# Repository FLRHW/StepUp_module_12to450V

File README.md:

<p align="center" width="100%">
  
</p>

***

<p align="center">
  
&nbsp; &nbsp; &nbsp; &nbsp;
  
</p>

***

# **StepUp_module_12to450V**
This repository contains a reverse‑engineered KiCad schematic and PCB layout from a commercial module originally purchased from AliExpress.

## Project overview
This project documents the electrical design and PCB layout of a third‑party module by recreating them from scratch in KiCad for learning, repair, and interoperability purposes. The repository does not include any original vendor design files, firmware, branding, or trademarks.

## Origin and scope
Original hardware: generic module purchased from AliExpress (exact vendor and listing may change over time, the following terms can help finding similar modules: "70W DC-DC 12V 24V To 200V-450V Voltage Adjustable Boost Power Converter Nixie Clock Tube Amplifier Capacitor Charging").  
Status: unofficial, reverse‑engineered reference design; not affiliated with, endorsed by, or supported by the original manufacturer or seller.  
Contents: KiCad schematic, PCB layout, netlists, and supporting documentation created from measurements and inspection of a physical unit.

## Intended use
This repository is intended for:
* Educational use and study of the circuit;
* Repair, modification, or replacement of compatible hardware;
* Integration into hobby or research projects, subject to any third‑party IP that may apply in your jurisdiction. Users are responsible for checking any patent, copyright, or regulatory constraints that may apply to their own use.

## License
The KiCad design files and documentation in this repository are released under the CERN Open Hardware Licence v2 – Permissive (CERN‑OHL‑P‑2.0). SPDX identifier: CERN-OHL-P-2.0 See the LICENSE file for the full legal text and conditions.  
In short and non‑legal terms, you are free to use, modify, manufacture, and distribute hardware based on these files, provided you respect attribution requirements and the terms in the license.

## Trademarks and third‑party rights
All product names, logos, and brands of the original module are the property of their respective owners and are not included or licensed here.  
Any reference to third‑party marks is purely descriptive and does not imply endorsement or affiliation.  
If you are the rights holder for the original hardware and have concerns about this documentation, please open an issue in the repository.

## Safety and disclaimer
* The design is provided as is, with no warranty of any kind;
* Use it at your own risk; always review the schematic, layout, and component ratings before using it;
* High voltage can cause injury, death, or damage to equipment; ensure appropriate protections and testing procedures.

## Contributing
Contributions are welcome. Please use pull requests and issues to propose changes or discuss potential improvements.

***

## DIRECTORY STRUCTURE
    │
    ├─ Computations       # Misc calculations
    ├─ HTML               # HTML files for generated webpage
    ├─ Images             # Pictures and renders
    │
    ├─ kibot_resources    # External resources for KiBot
    │  ├─ colors          # Color theme for KiCad
    │  ├─ fonts           # Fonts used in the project
    │  ├─ scripts         # External scripts used with KiBot
    │  └─ templates       # Templates for KiBot generated reports
    │
    ├─ kibot_yaml         # KiBot YAML config files
    ├─ KiRI               # KiRI (PCB diff viewer) files
    │
    ├─ lib                # KiCad footprint and symbol libraries
    │  ├─ 3d_models       # Component 3D models
    │  ├─ lib_fp          # Footprint libraries
    │  └─ lib_sym         # Symbol libraries
    │
    ├─ Logos              # Logos
    │
    ├─ Manufacturing      # Assembly and fabrication documents
    │  ├─ Assembly        # Assembly documents (BoM, pos, notes)
    │  │
    │  └─ Fabrication     # Fabrication documents (ZIP, notes)
    │     ├─ Drill Tables # CSV drill tables
    │     └─ Gerbers      # Gerbers
    │
    ├─ Report             # Reports for ERC/DRC
    ├─ Schematic          # PDF of schematic
    ├─ Supporting docs    # Measurement data
    │  ├─ 11.66 kOhm load # Scope captures
    │  └─ 870 Ohm load    # Scope captures
    │
	├─ Templates          # Title block templates
    ├─ Testing
    │  └─ Testpoints      # Testpoints tables      
    │
    └─ Variants           # Outputs for assembly variants

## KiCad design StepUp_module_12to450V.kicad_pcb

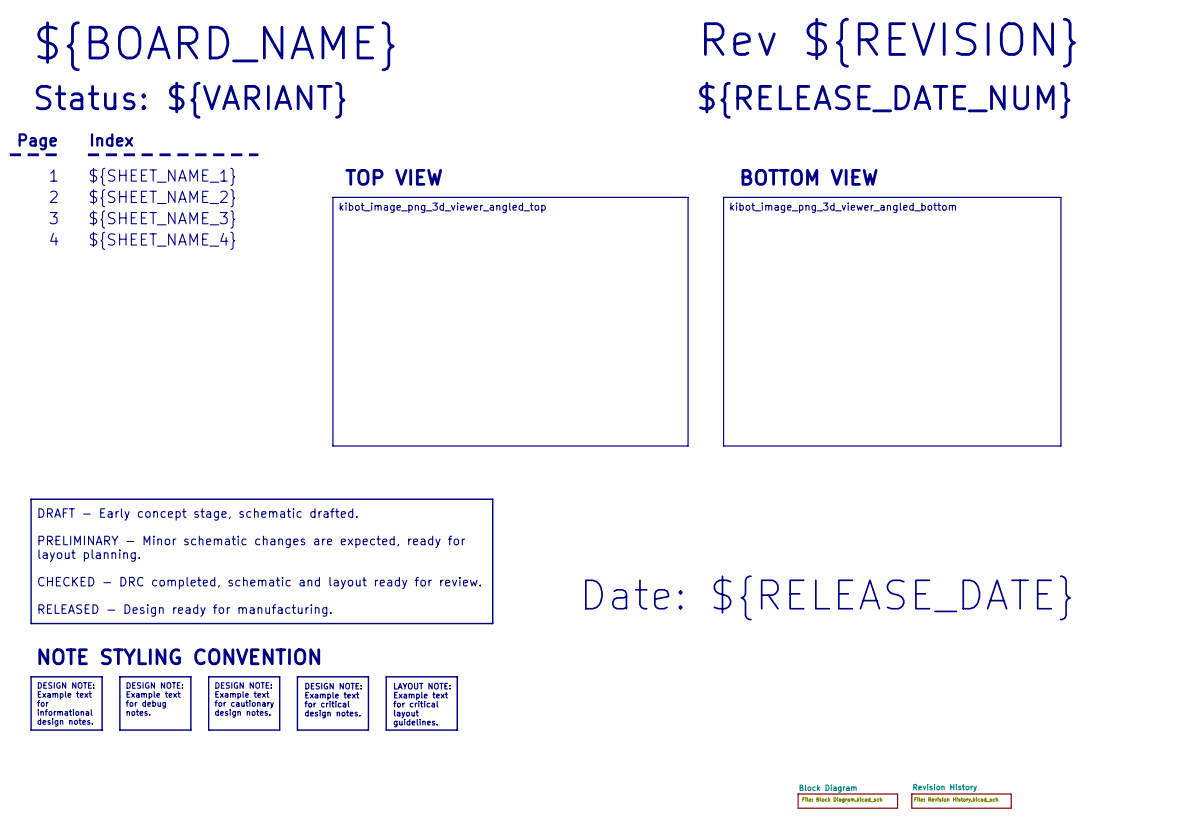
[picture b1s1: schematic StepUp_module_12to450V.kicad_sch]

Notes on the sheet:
Status: ${VARIANT}
${SHEET_NAME_2}
Page
${RELEASE_DATE_NUM}
Rev ${REVISION}
BOTTOM VIEW
Date: ${RELEASE_DATE}
${BOARD_NAME}
${SHEET_NAME_1}
${SHEET_NAME_3}
TOP VIEW
Index
${SHEET_NAME_4}
NOTE STYLING CONVENTION
DESIGN NOTE: Example text for cautionary design notes.
DESIGN NOTE: Example text for debug notes.
DESIGN NOTE: Example text for critical design notes.
LAYOUT NOTE: Example text for critical layout guidelines.
kibot_image_png_3d_viewer_angled_bottom
DESIGN NOTE: Example text for informational design notes.
kibot_image_png_3d_viewer_angled_top
DRAFT - Early concept stage, schematic drafted. PRELIMINARY - Minor schematic changes are expected, ready for layout planning. CHECKED - DRC completed, schematic and layout ready for review. RELEASED - Design ready for manufacturing.

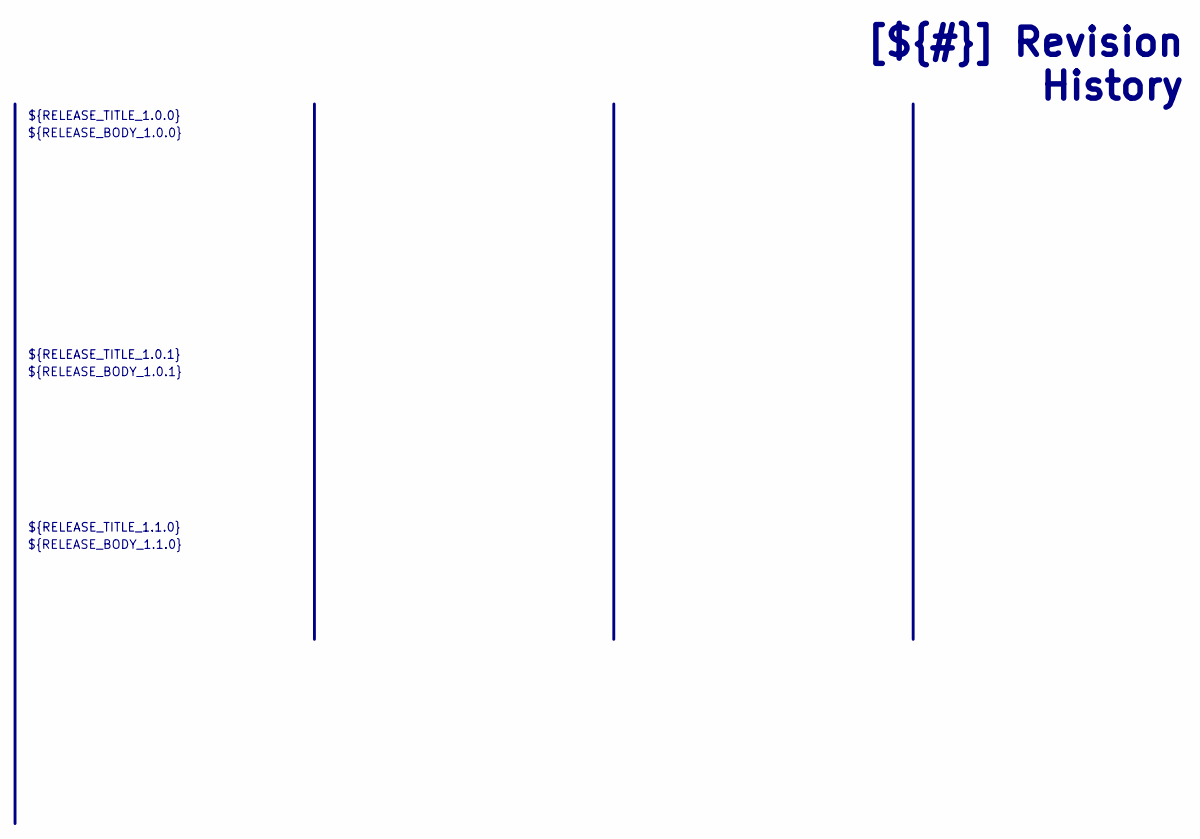
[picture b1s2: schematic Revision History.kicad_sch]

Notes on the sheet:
[${#}] ${TITLE}
${RELEASE_BODY_1.0.0}
${RELEASE_TITLE_1.1.0}
${RELEASE_BODY_1.1.0}
${RELEASE_BODY_1.0.1}
${RELEASE_TITLE_1.0.0}
${RELEASE_TITLE_1.0.1}

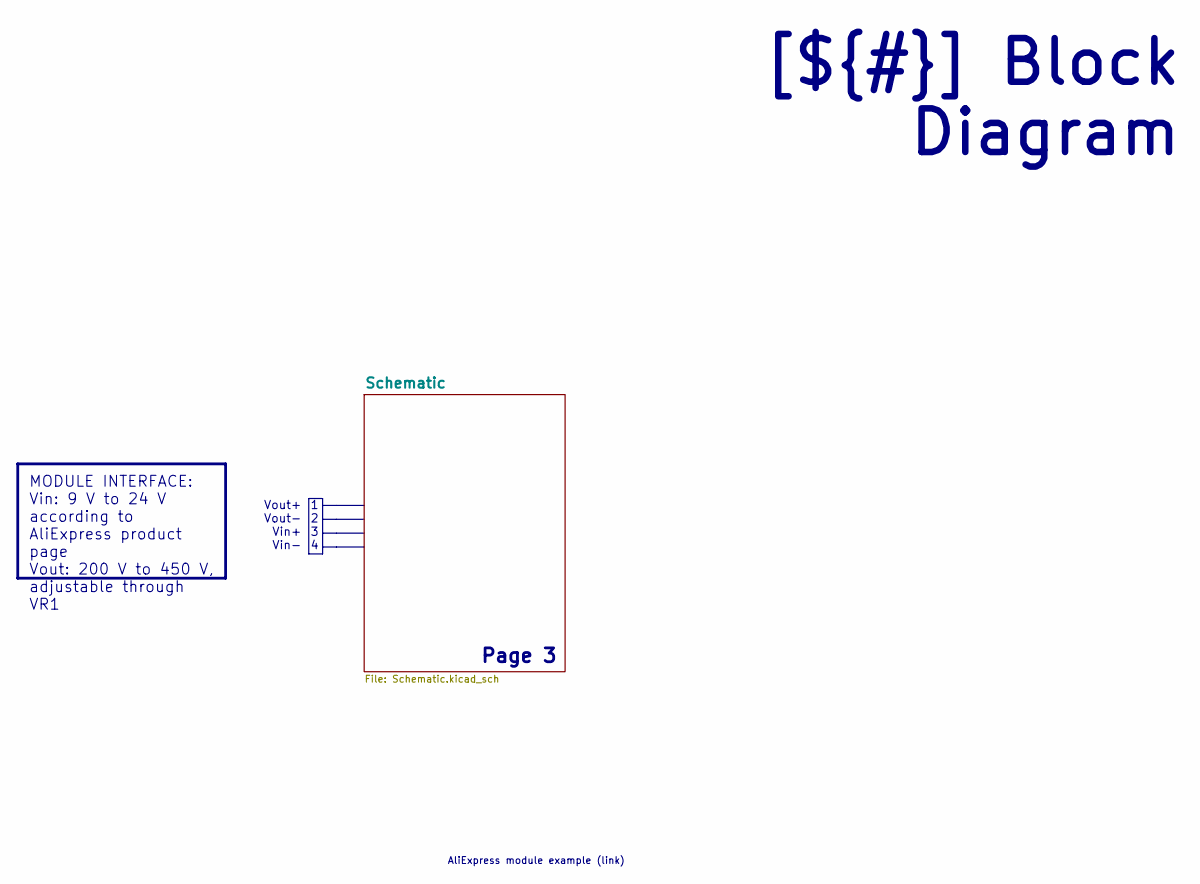
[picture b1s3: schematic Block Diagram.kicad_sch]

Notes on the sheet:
Page 3
1 2 3 4
Vout+ Vout- Vin+ Vin-
AliExpress module example (link)
MODULE INTERFACE: Vin: 9 V to 24 V according to AliExpress product page Vout: 200 V to 450 V, adjustable through VR1
[${#}] ${TITLE}

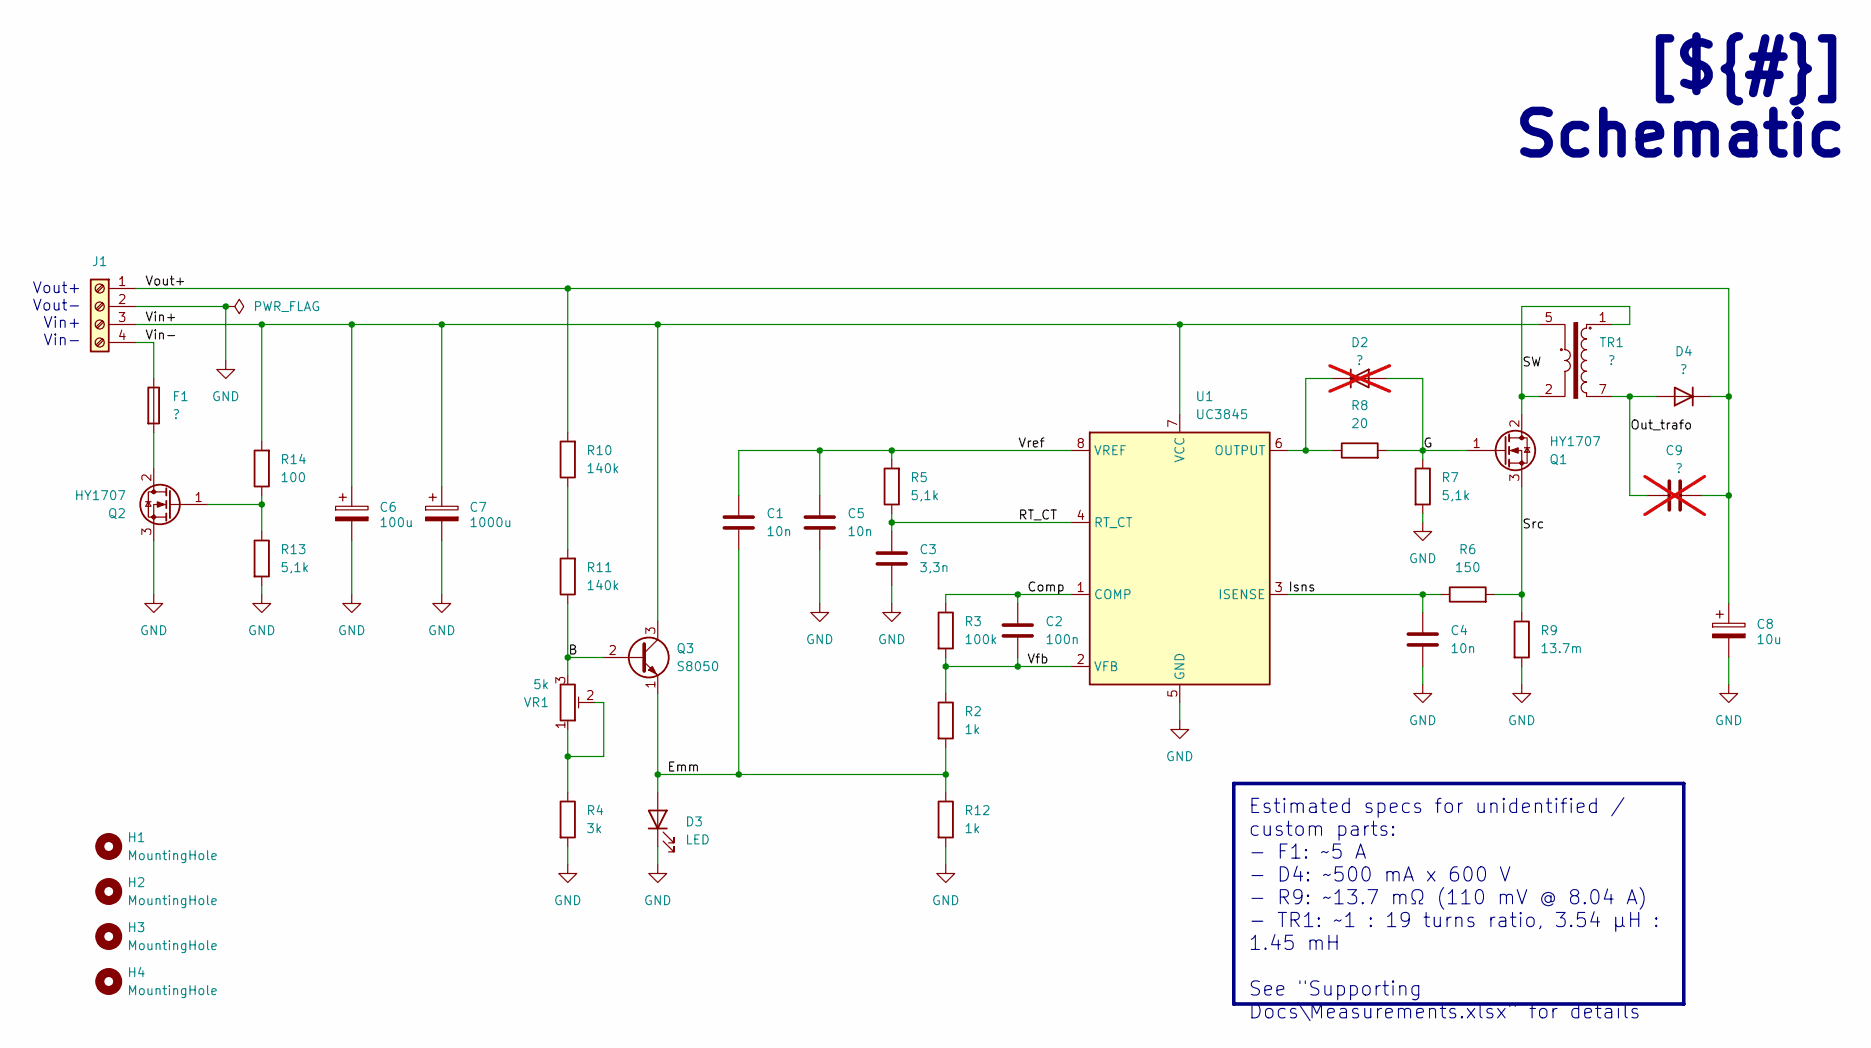
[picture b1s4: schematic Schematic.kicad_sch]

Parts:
C1, C4, C5: 10n; C_Rect_L7.0mm_W2.0mm_P5.00mm
C2: 100n; C_Disc_D4.3mm_W1.9mm_P5.00mm
C3: 3,3n; C_Rect_L7.0mm_W2.0mm_P5.00mm
C6: 100u; C_Radial_D8.0mm_H11.5mm_P3.50mm
C7: 1000u; C_Radial_D10.0mm_H20.0mm_P5.00mm
C8: 10u; C_Radial_D10.0mm_H16.0mm_P5.00mm
C9: ?; C_Rect_L7.0mm_W2.0mm_P5.00mm; not fitted
D2: ?; D_A-405_P7.62mm_Horizontal; not fitted
D3: LED; LED_D3.0mm
D4: ?; D_A-405_P10.16mm_Horizontal
F1: ?; Fuseholder_Clip-5x20mm_Eaton_1A5601-01_Inline_P20.80x6.76mm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
H1, H2, H3, H4: MountingHole; MountingHole_2.1mm
J1: Screw_Terminal_01x04; TerminalBlock_Phoenix_MKDS-1,5-4_1x04_P5.00mm_Horizontal
Q1, Q2: HY1707; TO-220F-3_Vertical
Q3: S8050; TO-92_Inline_Wide
R2, R12: 1k; R_Axial_DIN0207_L6.3mm_D2.5mm_P7.62mm_Horizontal
R3: 100k; R_Axial_DIN0207_L6.3mm_D2.5mm_P7.62mm_Horizontal
R4: 3k; R_Axial_DIN0207_L6.3mm_D2.5mm_P7.62mm_Horizontal
R5, R7, R13: 5,1k; R_Axial_DIN0207_L6.3mm_D2.5mm_P7.62mm_Horizontal
R6: 150; R_Axial_DIN0309_L9.0mm_D3.2mm_P12.70mm_Horizontal
R8: 20; R_Axial_DIN0207_L6.3mm_D2.5mm_P7.62mm_Horizontal
R9: 13.7m; R_Axial_DIN0309_L9.0mm_D3.2mm_P15.24mm_Horizontal
R10, R11: 140k; R_Axial_DIN0309_L9.0mm_D3.2mm_P12.70mm_Horizontal
R14: 100; R_Axial_DIN0207_L6.3mm_D2.5mm_P7.62mm_Horizontal
TR1: ?; Tr12to450V_Alixp
U1: UC3845; DIP-8_W7.62mm
VR1: 5k; Potentiometer_Bourns_3296W_Vertical

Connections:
/Block Diagram/Schematic/B: Q3.2 (B), R11.1, VR1.3
/Block Diagram/Schematic/Comp: C2.1, R3.1, U1.1 (COMP)
/Block Diagram/Schematic/Emm: C1.1, D3.2 (A), Q3.1 (E), R2.2, R12.1
/Block Diagram/Schematic/G: D2.2 (A), Q1.1 (G), R7.1, R8.2
/Block Diagram/Schematic/Isns: C4.1, R6.1, U1.3 (ISENSE)
/Block Diagram/Schematic/Out_trafo: C9.1, D4.2 (A), TR1.7
/Block Diagram/Schematic/RT_CT: C3.1, R5.1, U1.4 (RT_CT)
/Block Diagram/Schematic/SW: Q1.2 (D), TR1.1, TR1.2
/Block Diagram/Schematic/Src: Q1.3 (S), R6.2, R9.1
/Block Diagram/Schematic/Vfb: C2.2, R2.1, R3.2, U1.2 (VFB)
/Block Diagram/Schematic/Vin+: C6.1, C7.1, J1.3, Q3.3 (C), R14.2, TR1.5, U1.7 (VCC)
/Block Diagram/Schematic/Vin-: F1.1, J1.4
/Block Diagram/Schematic/Vout+: C8.1, C9.2, D4.1 (K), J1.1, R10.2
/Block Diagram/Schematic/Vref: C1.2, C5.1, R5.2, U1.8 (VREF)
GND: C3.2, C4.2, C5.2, C6.2, C7.2, C8.2, D3.1 (K), J1.2, Q2.3 (S), R4.2, R7.2, R9.2, R12.2, R13.2, U1.5 (GND)
unnamed: D2.1 (K), R8.1, U1.6 (OUTPUT)
unnamed: F1.2, Q2.2 (D)
unnamed: Q2.1 (G), R13.1, R14.1
unnamed: R4.1, VR1.1, VR1.2
unnamed: R10.1, R11.2

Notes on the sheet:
Vout+ Vout- Vin+ Vin-
[${#}] ${TITLE}
Estimated specs for unidentified / custom parts: - F1: ~5 A - D4: ~500 mA x 600 V - R9: ~13.7 mΩ (110 mV @ 8.04 A) - TR1: ~1 : 19 turns ratio, 3.54 μH : 1.45 mH See "Supporting Docs\Measurements.xlsx" for details

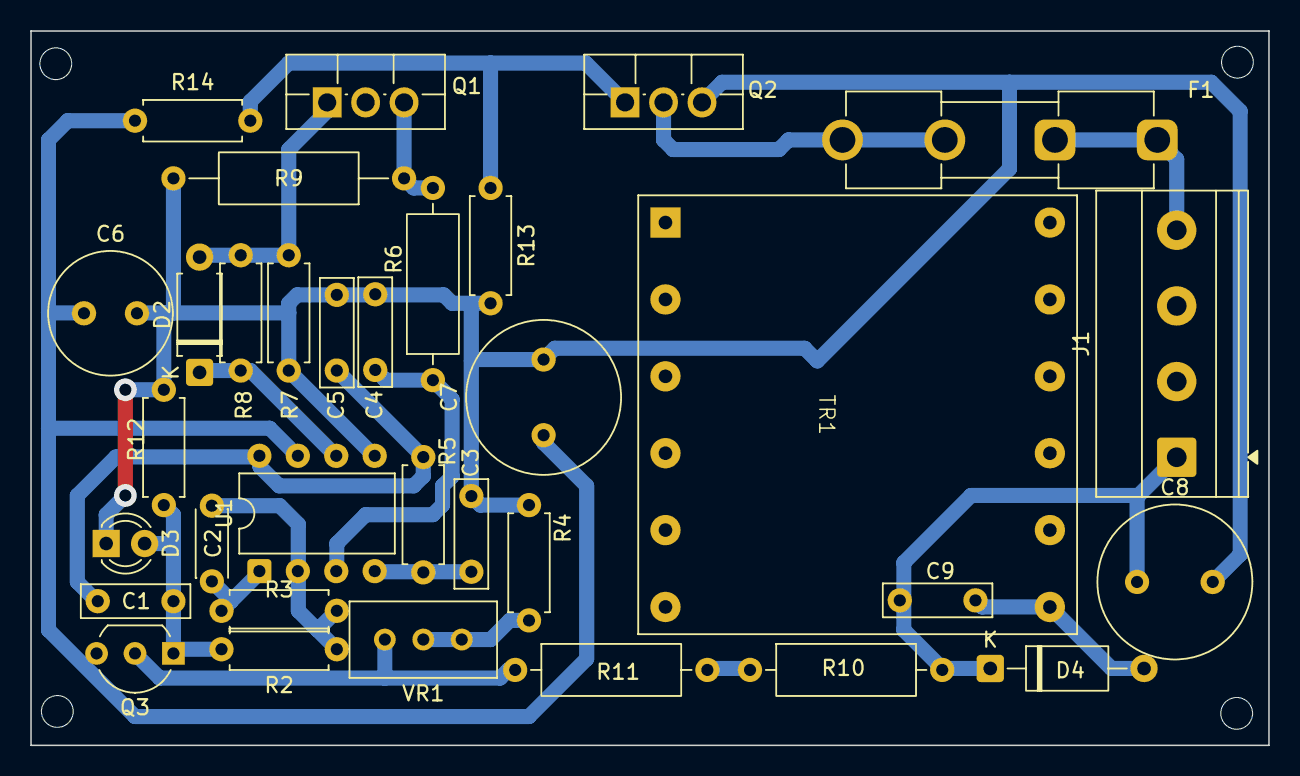
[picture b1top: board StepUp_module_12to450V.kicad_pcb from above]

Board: 2 copper layers, 81.8 x 47.2 mm, 37 parts (0 on the bottom side), 20 nets.

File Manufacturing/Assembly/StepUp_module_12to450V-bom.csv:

Row,Quantity Per PCB,References,Value,Datasheet,Footprint,Description,Manufacturer,Manufacturer Part Number,Supplier Part Number
1,3,C1 C4 C5,10n,~,C_Rect_L7.0mm_W2.0mm_P5.00mm,Unpolarized capacitor,,,
2,1,C3,"3,3n",~,C_Rect_L7.0mm_W2.0mm_P5.00mm,Unpolarized capacitor,,,
3,1,C2,100n,~,C_Disc_D4.3mm_W1.9mm_P5.00mm,Unpolarized capacitor,,,
4,1,C8,10u,~,C_Radial_D10.0mm_H16.0mm_P5.00mm,Polarized capacitor,,,
5,1,C6,100u,~,C_Radial_D8.0mm_H11.5mm_P3.50mm,Polarized capacitor,,,
6,1,C7,1000u,~,C_Radial_D10.0mm_H20.0mm_P5.00mm,Polarized capacitor,,,
7,3,D4 F1 TR1,?,~,D_A-405_P10.16mm_Horizontal,Diode Fuse,,,
8,1,D3,LED,~,LED_D3.0mm,Light emitting diode,,,
9,1,J1,Screw_Terminal_01x04,~,"TerminalBlock_Phoenix_MKDS-1,5-4_1x04_P5.00mm_Horizontal","Generic screw terminal, single row, 01x04, script generated (kicad-library-utils/schlib/autogen/connector/)",,,
10,2,Q1 Q2,HY1707,~,TO-220F-3_Vertical,"N-MOSFET transistor, gate/drain/source",,,
11,1,Q3,S8050,http://www.unisonic.com.tw/datasheet/S8050.pdf,TO-92_Inline_Wide,"0.7A Ic, 20V Vce, Low Voltage High Current NPN Transistor, TO-92",,,
12,1,R9,13.7m,~,R_Axial_DIN0309_L9.0mm_D3.2mm_P15.24mm_Horizontal,Resistor,,,
13,1,R8,20,~,R_Axial_DIN0207_L6.3mm_D2.5mm_P7.62mm_Horizontal,Resistor,,,
14,1,R14,100,~,R_Axial_DIN0207_L6.3mm_D2.5mm_P7.62mm_Horizontal,Resistor,,,
15,1,R6,150,~,R_Axial_DIN0309_L9.0mm_D3.2mm_P12.70mm_Horizontal,Resistor,,,
16,2,R2 R12,1k,~,R_Axial_DIN0207_L6.3mm_D2.5mm_P7.62mm_Horizontal,Resistor,,,
17,1,R4,3k,~,R_Axial_DIN0207_L6.3mm_D2.5mm_P7.62mm_Horizontal,Resistor,,,
18,3,R5 R7 R13,"5,1k",~,R_Axial_DIN0207_L6.3mm_D2.5mm_P7.62mm_Horizontal,Resistor,,,
19,1,R3,100k,~,R_Axial_DIN0207_L6.3mm_D2.5mm_P7.62mm_Horizontal,Resistor,,,
20,2,R10 R11,140k,~,R_Axial_DIN0309_L9.0mm_D3.2mm_P12.70mm_Horizontal,Resistor,,,
21,1,U1,UC3845,,DIP-8_W7.62mm,,,,
22,1,VR1,5k,~,Potentiometer_Bourns_3296W_Vertical,Trim-potentiometer,,,

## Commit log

2025-12-12 Initial commit. Schematic capture and PCB layout replication nearly complete
2025-12-12 Update Outputs
2025-12-12 Updated readme file
2025-12-12 Moved to preliminary
2025-12-13 updated gitignore
2025-12-13 added trafo 3d model
2025-12-13 Refreshed trafo symbol and footprint
2025-12-13 Updated readme template and status notes
2025-12-13 Updated readme template, status comments and gitatributes
2025-12-13 Removed lib clone
2025-12-14 Testing new path for custom 3D model
2025-12-14 New 3D path for trafo
2025-12-14 Trying to solve TOC issues
2025-12-14 testing lib issue
2025-12-14 Updated some footpints
2025-12-14 Updated terminal block
2025-12-14 Updated top mask
2025-12-15 DRC completed, changed status to checked
2025-12-16 Rev history text added
2025-12-16 Trying to resolve CI issue
2025-12-17 Revert to DRC completed
2025-12-18 Replicated latest updates from Vincent's repo
2025-12-18 Reverted?
2025-12-19 Fixed PCB polygons
2025-12-19 Revert "Fixed PCB polygons"
    This reverts commit dcaf8486db0413924995f75ee6d491de60b936f0.
2025-12-19 Revert "Update Outputs"
    This reverts commit f9744f7c91168a221b7741dfeae28b67c08d2c58.
2025-12-19 Fix only polyg
2025-12-19 DBG1
2025-12-19 DBG2
2025-12-19 DBG3
2025-12-19 DBG4
2025-12-19 DBG5
2025-12-19 DBG6
2025-12-19 DBG7
2025-12-19 DBG8
2025-12-19 DBG9
2025-12-19 DBG10
2025-12-19 DBG11
2025-12-19 DBG13
2025-12-19 DBG14
2025-12-19 DBG15
2025-12-19 DBG16
2025-12-19 DBG17
2025-12-19 DBG18
2025-12-19 Preping release 1.0.0
2025-12-19 Restoring
2025-12-19 Solving rev hist
2025-12-19 Solving rev hist again
2025-12-19 Once more...
2025-12-20 Rev hist update
2025-12-20 Rev hist still
2025-12-20 Added notes for unidentified parts
2025-12-20 General notes added
2025-12-20 Update CHANGELOG
2025-12-20 Update Outputs (release)
2025-12-21 Fixed changelog
2025-12-21 Testing changelog issue
2025-12-21 Forcing CI
2026-01-16 Updated switcher IC
2026-01-16 Fixed ci and kibot_main, fixed DRC issue
2026-01-16 Reverted changelog file to debug issue
2026-01-16 Fixed pre_set_text and restored changelog
2026-01-16 fixed another issue in pre_set_text
2026-01-16 resolving corrupted project
2026-01-16 removed unresolved text boxes
2026-01-17 Test 1
2026-01-17 Ready to release
